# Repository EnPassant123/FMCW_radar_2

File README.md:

**FMCW Radar Project**

Contains design files, Verilog code for FPGA, and C code for computer.

Can be easily modified to act as a data streaming board (just disable sweep)

Code is still very buggy and does not pass timing. Use at your own risk!

Untested PCB changes: Added LDO to cut down on power supply noise (from USB) more.

The C code is based on libftdi1, and some changes need to be made to ftdi_stream.c

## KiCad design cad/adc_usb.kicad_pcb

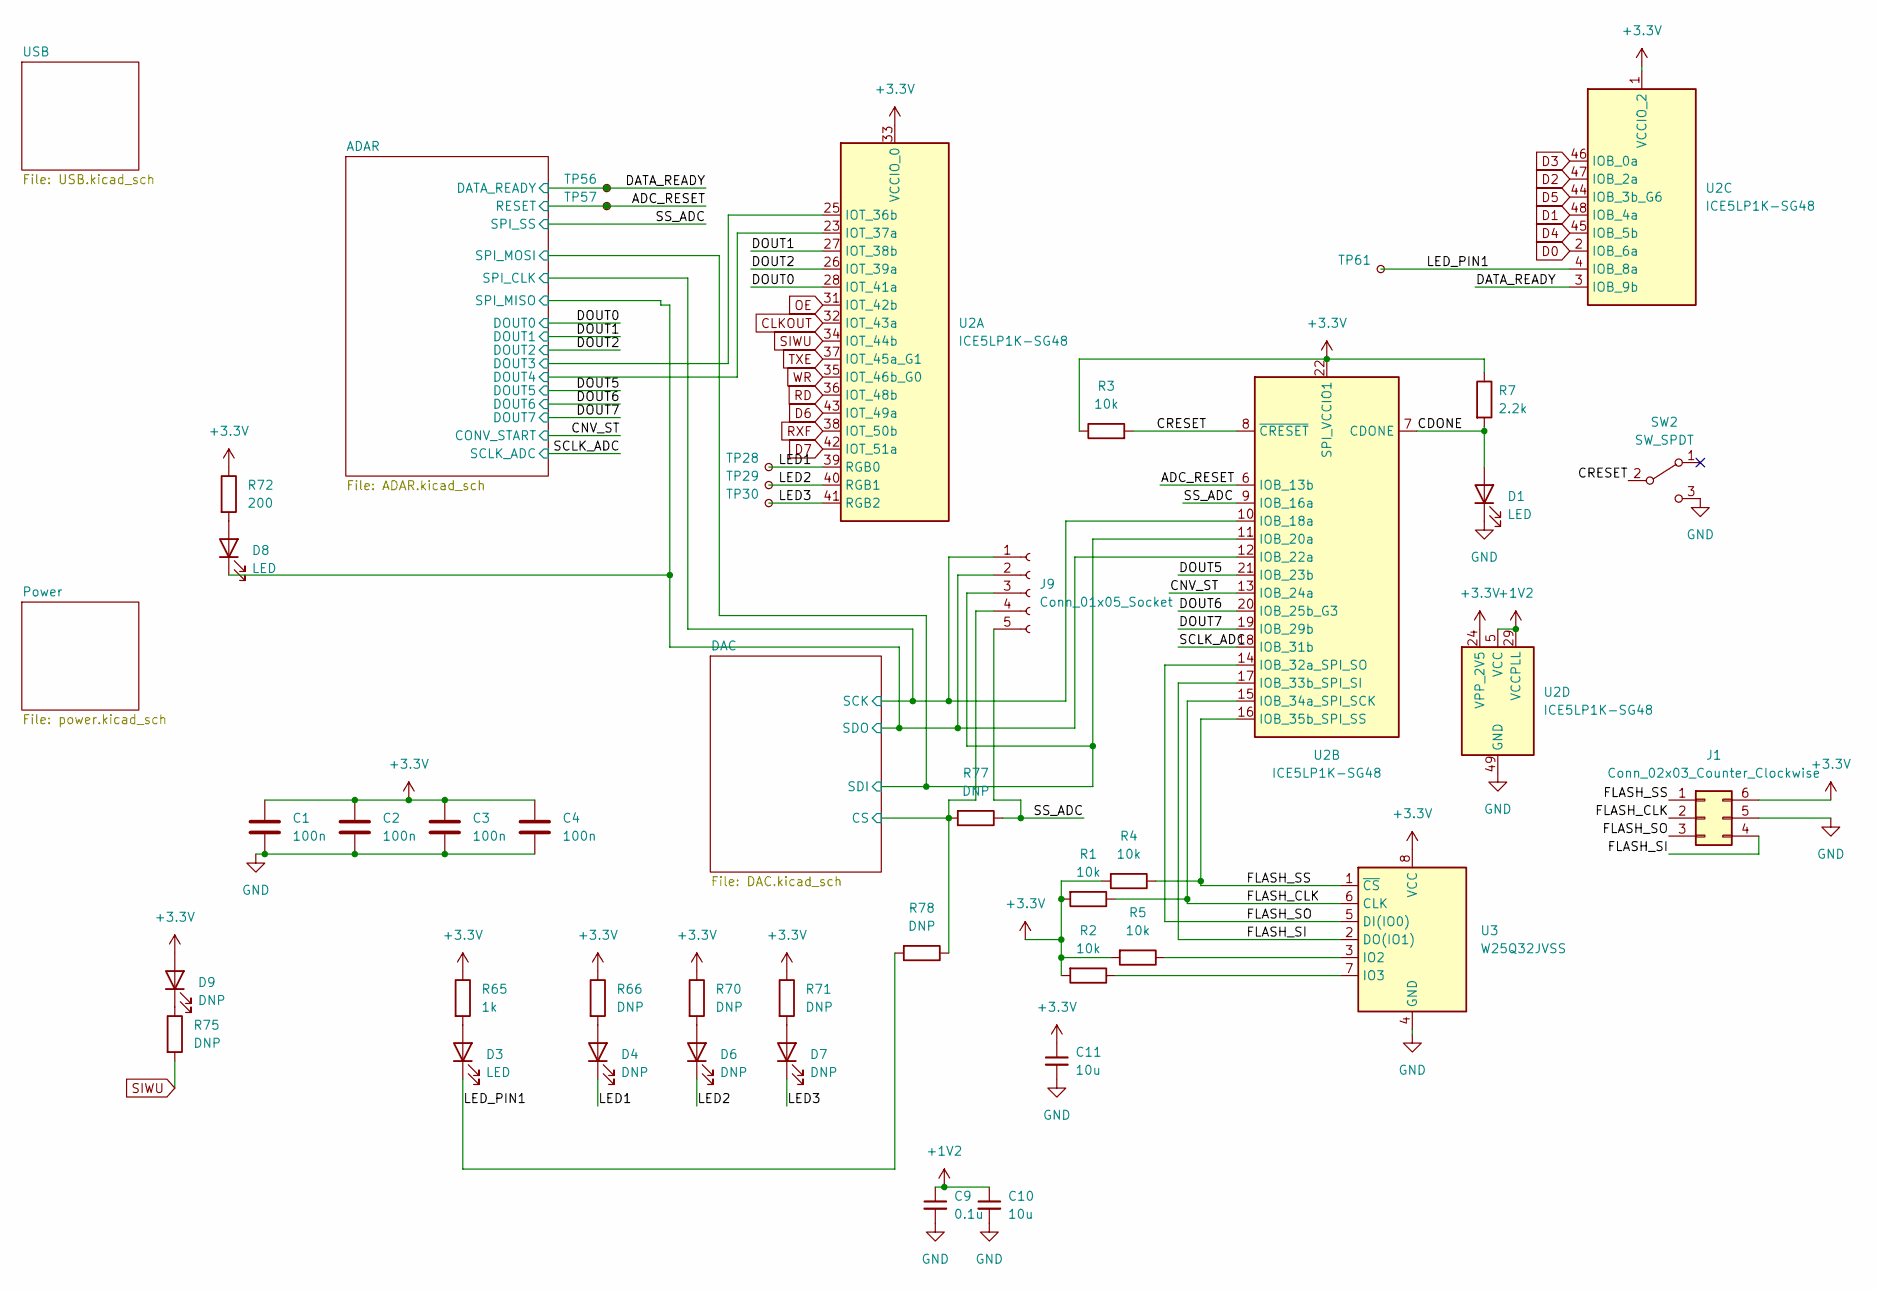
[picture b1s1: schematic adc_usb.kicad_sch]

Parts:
C1, C2, C3, C4: 100n; C_0603_1608Metric
C9: 0.1u; C_0603_1608Metric
C10, C11: 10u; C_0603_1608Metric
D1, D3, D8: LED; LED_1206_3216Metric
D4, D6, D7, D9: DNP; LED_1206_3216Metric
J1: Conn_02x03_Counter_Clockwise; PinSocket_2x03_P2.54mm_Vertical
J9: Conn_01x05_Socket; PinSocket_1x05_P2.54mm_Vertical
R1, R2, R3, R4, R5: 10k; R_0603_1608Metric
R7: 2.2k; R_0603_1608Metric
R65: 1k; R_0603_1608Metric
R66, R70, R71, R75, R77, R78: DNP; R_0603_1608Metric
R72: 200; R_0603_1608Metric
SW2: SW_SPDT; PinHeader_1x03_P2.54mm_Vertical
TP28, TP29, TP30, TP56, TP57, TP61: TestPoint_Small; TestPoint_Pad_1.0x1.0mm
U2: ICE5LP1K-SG48; QFN-48-1EP_7x7mm_P0.5mm_EP5.6x5.6mm
U3: W25Q32JVSS; SOIC-8_5.23x5.23mm_P1.27mm

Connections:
+1V2: C9.1, C10.1, U2.5 (VCC), U2.29 (VCCPLL), U2.30 (VCC); also elsewhere on the board
+3.3V: C1.1, C2.1, C3.1, C4.1, C11.1, D9.2 (A), J1.6, R1.2, R2.2, R3.1, R4.2, R5.2, R7.1, R65.1, R66.1, R70.1, R71.1, R72.1, U2.1 (VCCIO_2), U2.22 (SPI_VCCIO1), U2.24 (VPP_2V5), U2.33 (VCCIO_0), U3.8 (VCC); also elsewhere on the board
/ADAR/DOUT3: U2.25 (IOT_36b); also elsewhere on the board
/ADAR/DOUT4: U2.23 (IOT_37a); also elsewhere on the board
/ADAR/SPI_CLK: J9.1, U2.10 (IOB_18a); also elsewhere on the board
/ADAR/SPI_MISO: D8.1 (K), J9.2, U2.12 (IOB_22a); also elsewhere on the board
/ADAR/SPI_MOSI: J9.3, U2.11 (IOB_20a); also elsewhere on the board
/ADC_RESET: TP57.1, U2.6 (IOB_13b); also elsewhere on the board
/CDONE: D1.2 (A), R7.2, U2.7 (CDONE)
/CNV_ST: U2.13 (IOB_24a); also elsewhere on the board
/CRESET: R3.2, SW2.2 (B), U2.8 (~CRESET)
/DAC/CS: J9.4, R77.2, R78.1; also elsewhere on the board
/DATA_READY: TP56.1, U2.3 (IOB_9b); also elsewhere on the board
/DOUT0: U2.28 (IOT_41a); also elsewhere on the board
/DOUT1: U2.27 (IOT_38b); also elsewhere on the board
/DOUT2: U2.26 (IOT_39a); also elsewhere on the board
/DOUT5: U2.21 (IOB_23b); also elsewhere on the board
/DOUT6: U2.20 (IOB_25b_G3); also elsewhere on the board
/DOUT7: U2.19 (IOB_29b); also elsewhere on the board
/FLASH_CLK: J1.2, R1.1, U2.15 (IOB_34a_SPI_SCK), U3.6 (CLK)
/FLASH_SI: J1.4, U2.17 (IOB_33b_SPI_SI), U3.2 (DO(IO1))
/FLASH_SO: J1.3, U2.14 (IOB_32a_SPI_SO), U3.5 (DI(IO0))
/FLASH_SS: J1.1, R4.1, U2.16 (IOB_35b_SPI_SS), U3.1 (~CS)
/LED1: D4.1 (K), TP28.1, U2.39 (RGB0)
/LED2: D6.1 (K), TP29.1, U2.40 (RGB1)
/LED3: D7.1 (K), TP30.1, U2.41 (RGB2)
/LED_PIN1: D3.1 (K), R78.2, TP61.1, U2.4 (IOB_8a)
/SCLK_ADC: U2.18 (IOB_31b); also elsewhere on the board
/SS_ADC: J9.5, R77.1, U2.9 (IOB_16a); also elsewhere on the board
CLKOUT: U2.32 (IOT_43a); also elsewhere on the board
D0: U2.2 (IOB_6a); also elsewhere on the board
D1: U2.48 (IOB_4a); also elsewhere on the board
D2: U2.47 (IOB_2a); also elsewhere on the board
D3: U2.46 (IOB_0a); also elsewhere on the board
D4: U2.45 (IOB_5b); also elsewhere on the board
D5: U2.44 (IOB_3b_G6); also elsewhere on the board
D6: U2.43 (IOT_49a); also elsewhere on the board
D7: U2.42 (IOT_51a); also elsewhere on the board
GND: C1.2, C2.2, C3.2, C4.2, C9.2, C10.2, C11.2, D1.1 (K), J1.5, SW2.3 (C), U2.49 (GND), U3.4 (GND); also elsewhere on the board
unnamed: D3.2 (A), R65.2
unnamed: D4.2 (A), R66.2
unnamed: D6.2 (A), R70.2
unnamed: D7.2 (A), R71.2
unnamed: D8.2 (A), R72.2
unnamed: D9.1 (K), R75.1
unnamed: R5.1, U3.3 (IO2)
unnamed: R2.1, U3.7 (IO3)
OE: U2.31 (IOT_42b); also elsewhere on the board
RD: U2.36 (IOT_48b); also elsewhere on the board
RXF: U2.38 (IOT_50b); also elsewhere on the board
SIWU: R75.2, U2.34 (IOT_44b); also elsewhere on the board
TXE: U2.37 (IOT_45a_G1); also elsewhere on the board
WR: U2.35 (IOT_46b_G0); also elsewhere on the board

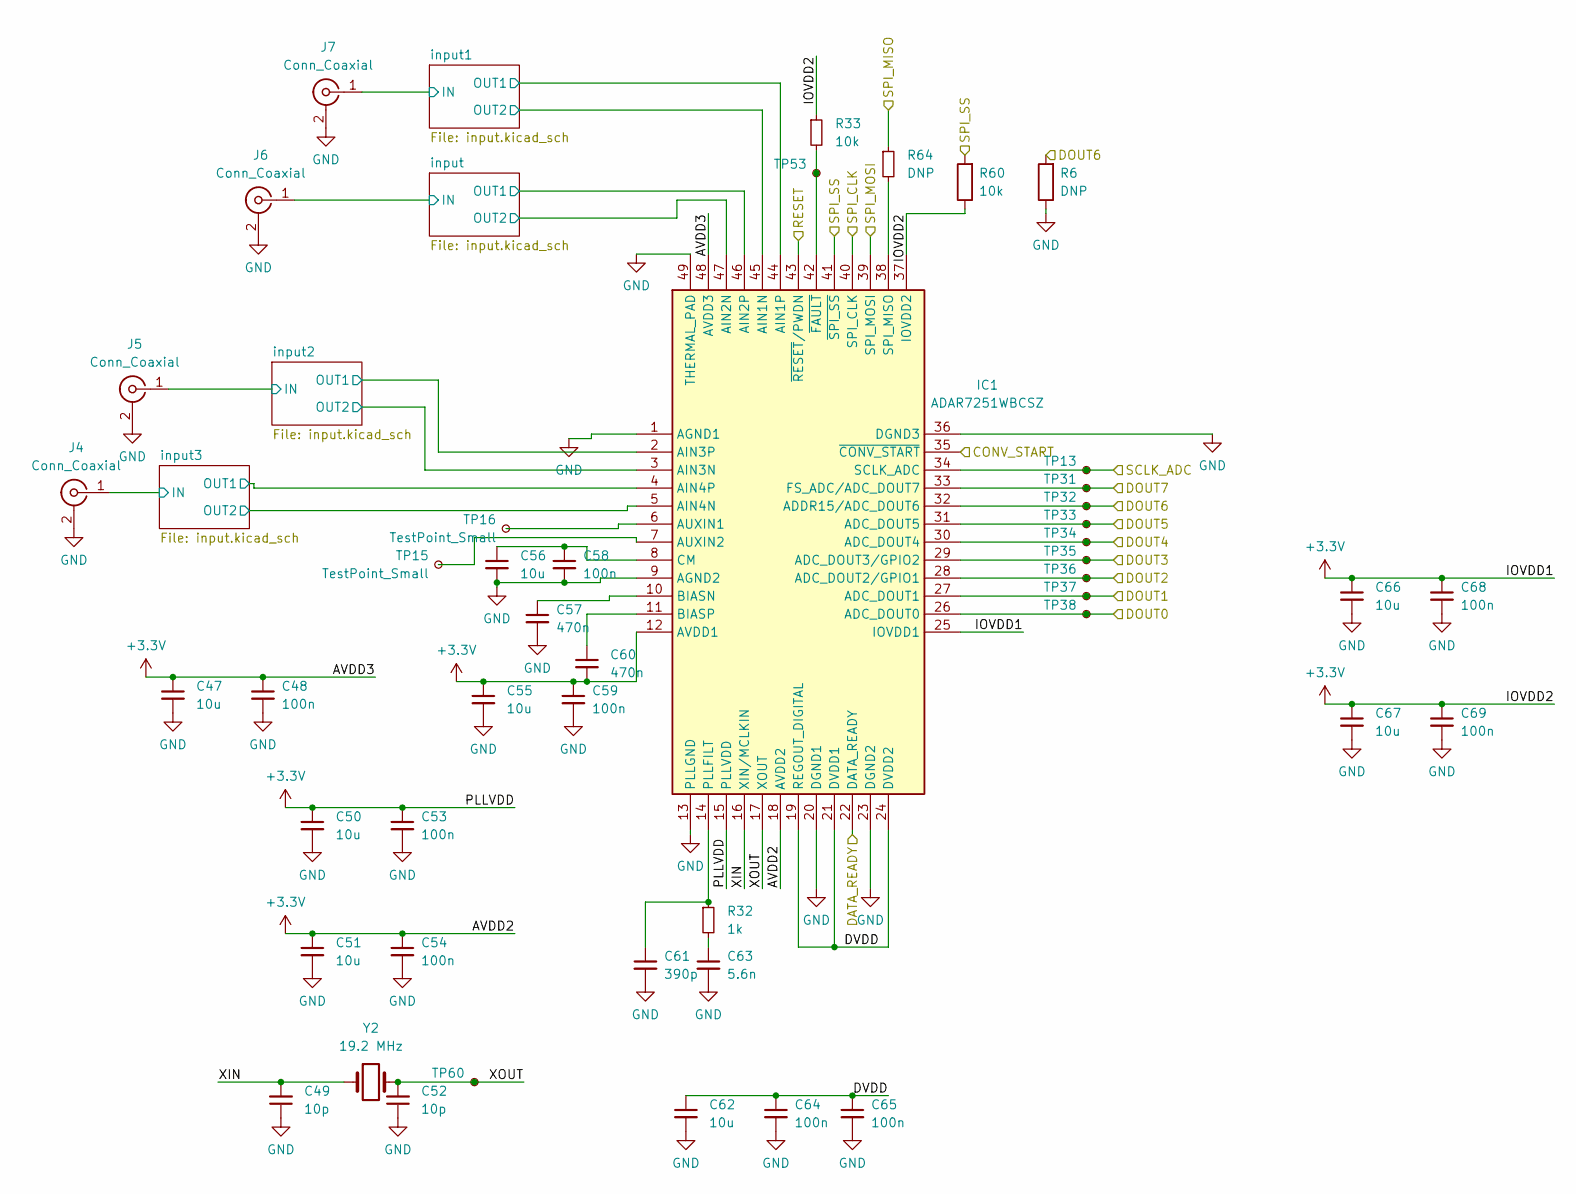
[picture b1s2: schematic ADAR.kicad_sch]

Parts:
C47, C50, C51, C55, C56, C62, C66, C67: 10u; C_0603_1608Metric
C48, C53, C54, C58, C59, C64, C65, C68, C69: 100n; C_0603_1608Metric
C49, C52: 10p; C_0603_1608Metric
C57, C60: 470n; C_0603_1608Metric
C61: 390p; C_0603_1608Metric
C63: 5.6n; C_0603_1608Metric
IC1: ADAR7251WBCSZ; LFCSP-48-1EP_7x7mm_P0.5mm_EP4.1x4.1mm; Manufacturer_Part_Number ADAR7251WBCSZ; Mouser Part Number 584-ADAR7251WBCSZ
J4, J5, J6, J7: Conn_Coaxial; SMA_Samtec_SMA-J-P-X-ST-EM1_EdgeMount
R6, R64: DNP; R_0603_1608Metric
R32: 1k; R_0603_1608Metric
R33, R60: 10k; R_0603_1608Metric
TP13, TP31, TP32, TP33, TP34, TP35, TP36, TP37, TP38, TP53: TestPoint_Small; TestPoint_Pad_1.0x1.0mm
TP15, TP16, TP60: TestPoint_Small; TestPoint_Pad_2.0x2.0mm
Y2: 19.2 MHz; Crystal_SMD_3225-4Pin_3.2x2.5mm

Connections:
+3.3V: C47.1, C48.1, C50.1, C51.1, C53.1, C54.1, C55.1, C59.1, C60.2, C66.1, C67.1, C68.1, C69.1, IC1.12 (AVDD1), IC1.15 (PLLVDD), IC1.18 (AVDD2), IC1.25 (IOVDD1), IC1.37 (IOVDD2), IC1.48 (AVDD3), R33.1, R60.1; also elsewhere on the board
/ADAR/DOUT3: IC1.29 (ADC_DOUT3/GPIO2), TP35.1; also elsewhere on the board
/ADAR/DOUT4: IC1.30 (ADC_DOUT4), TP34.1; also elsewhere on the board
/ADAR/DVDD: C62.1, C64.1, C65.1, IC1.19 (REGOUT_DIGITAL), IC1.21 (DVDD1), IC1.24 (DVDD2)
/ADAR/SPI_CLK: IC1.40 (SPI_CLK); also elsewhere on the board
/ADAR/SPI_MISO: R64.1; also elsewhere on the board
/ADAR/SPI_MOSI: IC1.39 (SPI_MOSI); also elsewhere on the board
/ADAR/XIN: C49.2, IC1.16 (XIN/MCLKIN), Y2.1
/ADAR/XOUT: C52.2, IC1.17 (XOUT), TP60.1, Y2.2
/ADAR/input1/OUT1: IC1.44 (AIN1P); also elsewhere on the board
/ADAR/input1/OUT2: IC1.45 (AIN1N); also elsewhere on the board
/ADAR/input2/IN: J5.1 (In); also elsewhere on the board
/ADAR/input2/OUT1: IC1.2 (AIN3P); also elsewhere on the board
/ADAR/input2/OUT2: IC1.3 (AIN3N); also elsewhere on the board
/ADAR/input3/OUT1: IC1.4 (AIN4P); also elsewhere on the board
/ADAR/input3/OUT2: IC1.5 (AIN4N); also elsewhere on the board
/ADAR/input/OUT1: IC1.46 (AIN2P); also elsewhere on the board
/ADAR/input/OUT2: IC1.47 (AIN2N); also elsewhere on the board
/ADC_RESET: IC1.43 (~RESET/PWDN); also elsewhere on the board
/CNV_ST: IC1.35 (~CONV_START); also elsewhere on the board
/DATA_READY: IC1.22 (DATA_READY); also elsewhere on the board
/DOUT0: IC1.26 (ADC_DOUT0), TP38.1; also elsewhere on the board
/DOUT1: IC1.27 (ADC_DOUT1), TP37.1; also elsewhere on the board
/DOUT2: IC1.28 (ADC_DOUT2/GPIO1), TP36.1; also elsewhere on the board
/DOUT5: IC1.31 (ADC_DOUT5), TP33.1; also elsewhere on the board
/DOUT6: IC1.32 (ADDR15/ADC_DOUT6), R6.2, TP32.1; also elsewhere on the board
/DOUT7: IC1.33 (FS_ADC/ADC_DOUT7), TP31.1; also elsewhere on the board
/SCLK_ADC: IC1.34 (SCLK_ADC), TP13.1; also elsewhere on the board
/SS_ADC: IC1.41 (~SPI_SS), R60.2; also elsewhere on the board
GND: C47.2, C48.2, C49.1, C50.2, C51.2, C52.1, C53.2, C54.2, C55.2, C56.2, C57.2, C58.2, C59.2, C61.2, C62.2, C63.2, C64.2, C65.2, C66.2, C67.2, C68.2, C69.2, IC1.1 (AGND1), IC1.9 (AGND2), IC1.13 (PLLGND), IC1.20 (DGND1), IC1.23 (DGND2), IC1.36 (DGND3), IC1.49 (THERMAL_PAD), J4.2 (Ext), J5.2 (Ext), J6.2 (Ext), J7.2 (Ext), R6.1; also elsewhere on the board
unnamed: C63.1, R32.2
unnamed: IC1.6 (AUXIN1), TP16.1
unnamed: IC1.7 (AUXIN2), TP15.1
unnamed: C57.1, IC1.10 (BIASN)
unnamed: C60.1, IC1.11 (BIASP)
unnamed: C56.1, C58.1, IC1.8 (CM)
unnamed: C61.1, IC1.14 (PLLFILT), R32.1
unnamed: IC1.38 (SPI_MISO), R64.2
unnamed: IC1.42 (~FAULT), R33.2, TP53.1

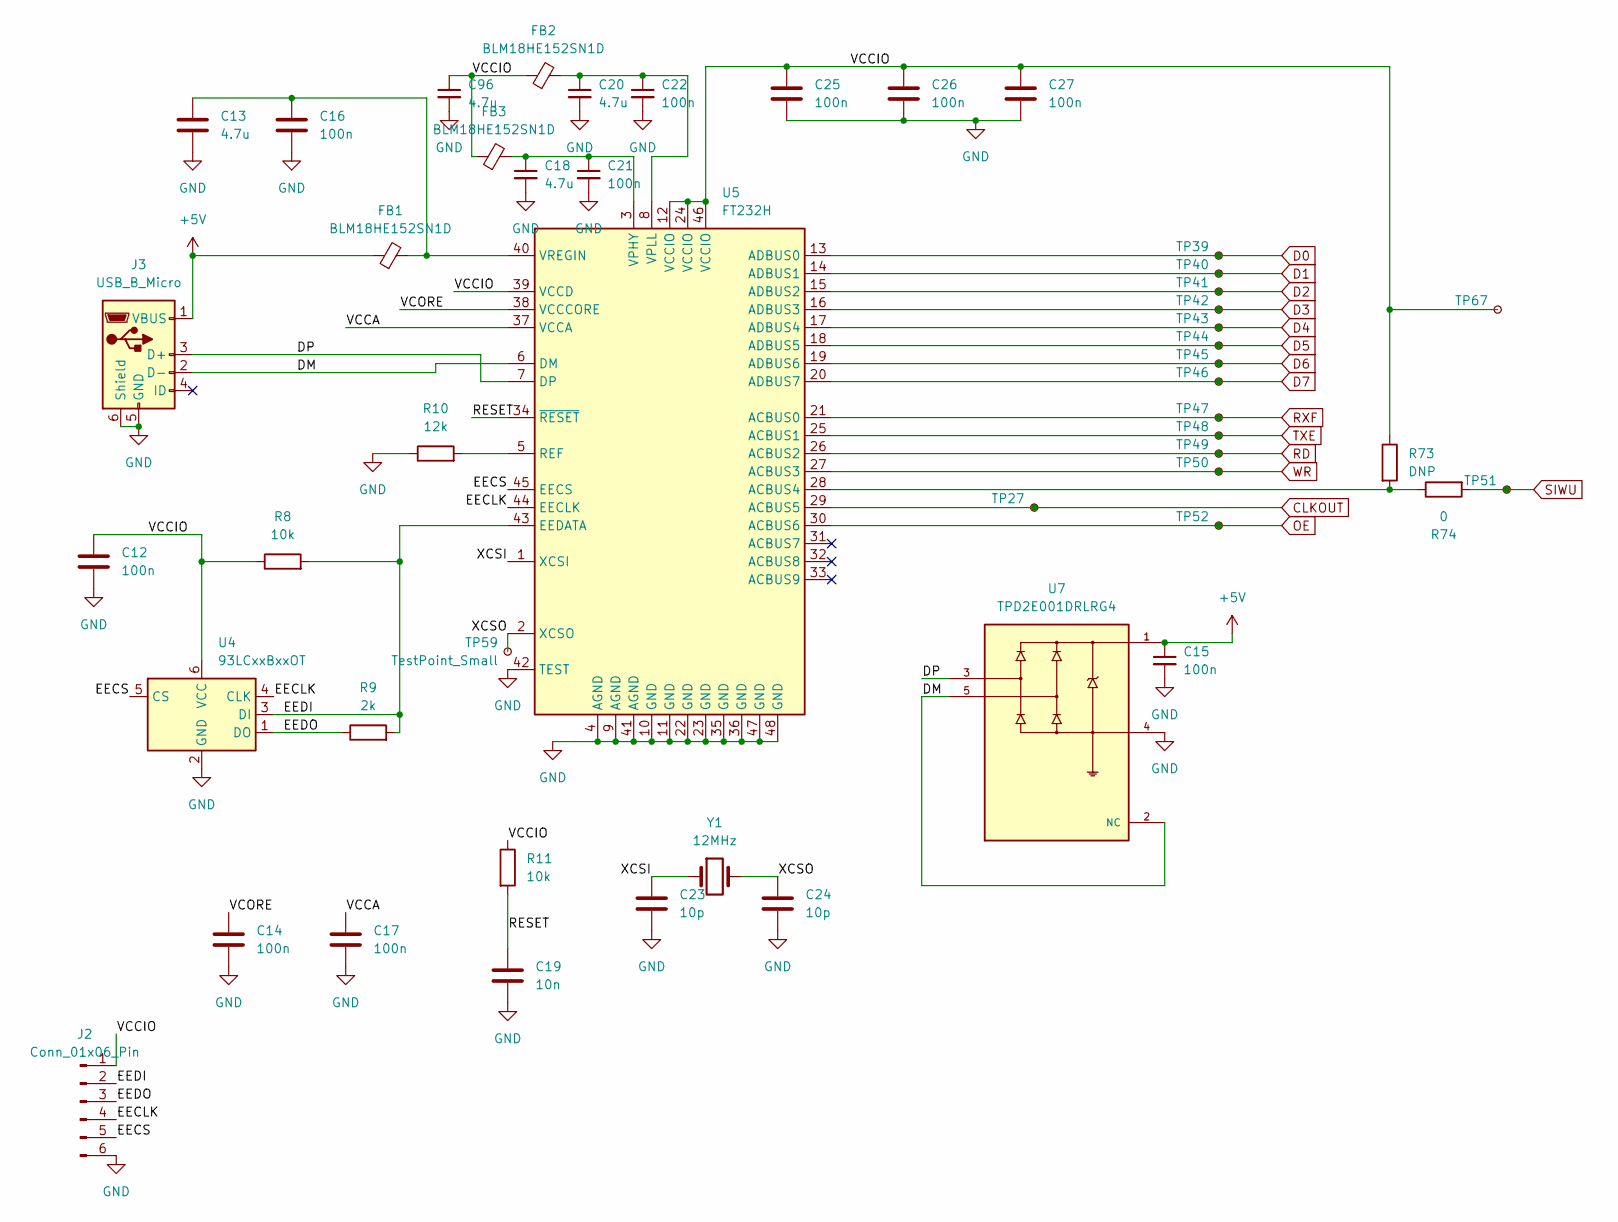
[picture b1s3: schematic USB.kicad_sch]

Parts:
C12, C14, C15, C16, C17, C21, C22, C25, C26, C27: 100n; C_0603_1608Metric
C13, C18, C20, C96: 4.7u; C_0603_1608Metric
C19: 10n; C_0603_1608Metric
C23, C24: 10p; C_0603_1608Metric
FB1, FB2, FB3: BLM18HE152SN1D; L_0603_1608Metric
J2: Conn_01x06_Pin; PinSocket_1x06_P2.54mm_Vertical
J3: USB_B_Micro; USB_Micro-B_Amphenol_10118193-0001LF_Horizontal
R8, R11: 10k; R_0603_1608Metric
R9: 2k; R_0603_1608Metric
R10: 12k; R_0603_1608Metric
R73: DNP; R_0603_1608Metric
R74: 0; R_0603_1608Metric
TP27, TP39, TP40, TP41, TP42, TP43, TP44, TP45, TP46, TP47, TP48, TP49, TP50, TP51, TP52, TP67: TestPoint_Small; TestPoint_Pad_1.0x1.0mm
TP59: TestPoint_Small; TestPoint_Pad_2.0x2.0mm
U4: 93LCxxBxxOT; SOT-23-6
U5: FT232H; LQFP-48_7x7mm_P0.5mm
U7: TPD2E001DRLRG4; SOT-553; PARTREV I
Y1: 12MHz; Crystal_SMD_3225-4Pin_3.2x2.5mm

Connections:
+5V: C15.1, FB1.1, J3.1 (VBUS), U7.1; also elsewhere on the board
/USB/DM: J3.2 (D-), U5.6 (DM), U7.2 (NC), U7.5
/USB/DP: J3.3 (D+), U5.7 (DP), U7.3
/USB/EECLK: J2.4, U4.4 (CLK), U5.44 (EECLK)
/USB/EECS: J2.5, U4.5 (CS), U5.45 (EECS)
/USB/EEDI: J2.2, R8.2, R9.2, U4.3 (DI), U5.43 (EEDATA)
/USB/EEDO: J2.3, R9.1, U4.1 (DO)
/USB/RESET: C19.1, R11.2, U5.34 (~RESET)
/USB/VCCA: C17.1, U5.37 (VCCA)
/USB/VCCIO: C12.1, C25.1, C26.1, C27.1, C96.1, FB2.1, FB3.1, J2.1, R8.1, R11.1, R73.1, TP67.1, U4.6 (VCC), U5.12 (VCCIO), U5.24 (VCCIO), U5.39 (VCCD), U5.46 (VCCIO)
/USB/VCORE: C14.1, U5.38 (VCCCORE)
/USB/XCSI: C23.1, U5.1 (XCSI), Y1.1
/USB/XCSO: C24.1, TP59.1, U5.2 (XCSO), Y1.2
CLKOUT: TP27.1, U5.29 (ACBUS5); also elsewhere on the board
D0: TP39.1, U5.13 (ADBUS0); also elsewhere on the board
D1: TP40.1, U5.14 (ADBUS1); also elsewhere on the board
D2: TP41.1, U5.15 (ADBUS2); also elsewhere on the board
D3: TP42.1, U5.16 (ADBUS3); also elsewhere on the board
D4: TP43.1, U5.17 (ADBUS4); also elsewhere on the board
D5: TP44.1, U5.18 (ADBUS5); also elsewhere on the board
D6: TP45.1, U5.19 (ADBUS6); also elsewhere on the board
D7: TP46.1, U5.20 (ADBUS7); also elsewhere on the board
GND: C12.2, C13.2, C14.2, C15.2, C16.2, C17.2, C18.2, C19.2, C20.2, C21.2, C22.2, C23.2, C24.2, C25.2, C26.2, C27.2, C96.2, J2.6, J3.5 (GND), J3.6 (Shield), R10.1, U4.2 (GND), U5.4 (AGND), U5.9 (AGND), U5.10 (GND), U5.11 (GND), U5.22 (GND), U5.23 (GND), U5.35 (GND), U5.36 (GND), U5.41 (AGND), U5.42 (TEST), U5.47 (GND), U5.48 (GND), U7.4; also elsewhere on the board
unnamed: R73.2, R74.1, U5.28 (ACBUS4)
unnamed: R10.2, U5.5 (REF)
unnamed: C18.1, C21.1, FB3.2, U5.3 (VPHY)
unnamed: C20.1, C22.1, FB2.2, U5.8 (VPLL)
unnamed: C13.1, C16.1, FB1.2, U5.40 (VREGIN)
OE: TP52.1, U5.30 (ACBUS6); also elsewhere on the board
RD: TP49.1, U5.26 (ACBUS2); also elsewhere on the board
RXF: TP47.1, U5.21 (ACBUS0); also elsewhere on the board
SIWU: R74.2, TP51.1; also elsewhere on the board
TXE: TP48.1, U5.25 (ACBUS1); also elsewhere on the board
WR: TP50.1, U5.27 (ACBUS3); also elsewhere on the board

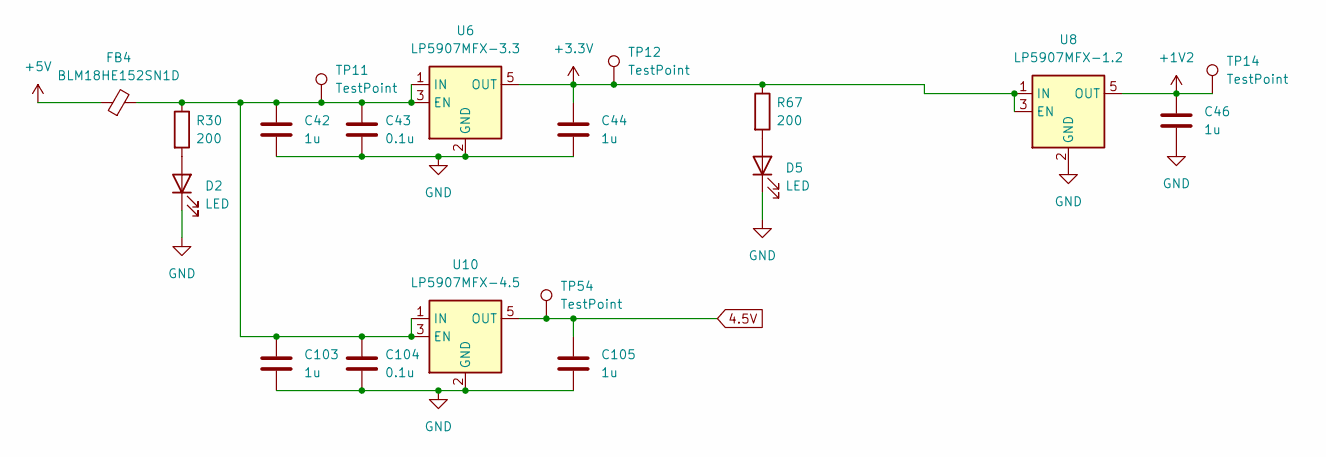
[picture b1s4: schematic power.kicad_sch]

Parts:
C42, C44, C46, C103, C105: 1u; C_0603_1608Metric
C43, C104: 0.1u; C_0603_1608Metric
D2, D5: LED; LED_1206_3216Metric
FB4: BLM18HE152SN1D; L_0603_1608Metric
R30, R67: 200; R_0603_1608Metric
TP11, TP12, TP14, TP54: TestPoint; TestPoint_Pad_2.0x2.0mm
U6: LP5907MFX-3.3; SOT-23-5
U8: LP5907MFX-1.2; SOT-23-5
U10: LP5907MFX-4.5; SOT-23-5

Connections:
4.5V: C105.1, TP54.1, U10.5 (OUT); also elsewhere on the board
+1V2: C46.1, TP14.1, U8.5 (OUT); also elsewhere on the board
+3.3V: C44.1, R67.1, TP12.1, U6.5 (OUT), U8.1 (IN), U8.3 (EN); also elsewhere on the board
+5V: FB4.1; also elsewhere on the board
GND: C42.2, C43.2, C44.2, C46.2, C103.2, C104.2, C105.2, D2.1 (K), D5.1 (K), U6.2 (GND), U8.2 (GND), U10.2 (GND); also elsewhere on the board
unnamed: D2.2 (A), R30.2
unnamed: D5.2 (A), R67.2
unnamed: C42.1, C43.1, C103.1, C104.1, FB4.2, R30.1, TP11.1, U6.1 (IN), U6.3 (EN), U10.1 (IN), U10.3 (EN)

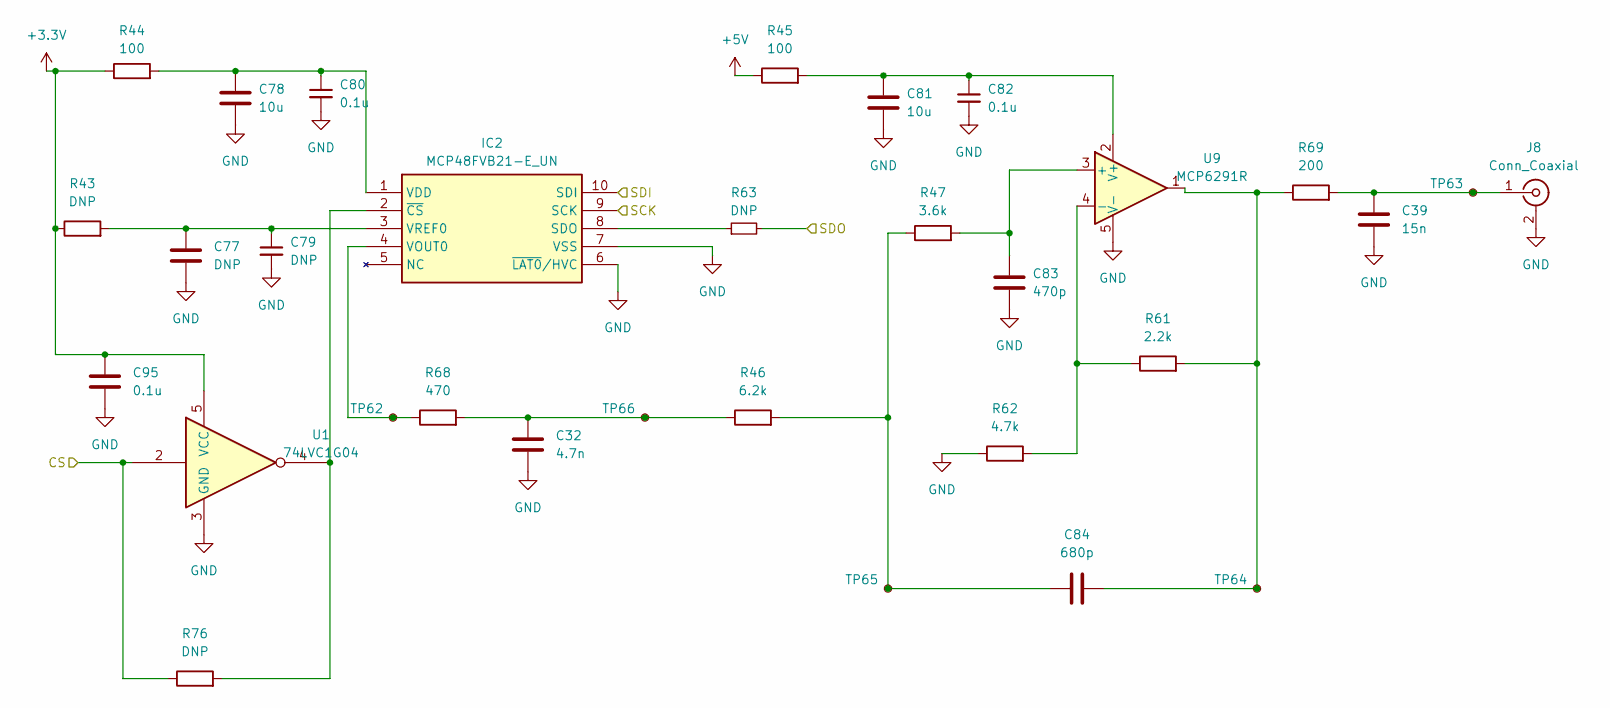
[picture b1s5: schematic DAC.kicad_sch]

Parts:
C32: 4.7n; C_0603_1608Metric
C39: 15n; C_0603_1608Metric
C77, C79: DNP; C_0603_1608Metric
C78, C81: 10u; C_0603_1608Metric
C80, C82, C95: 0.1u; C_0603_1608Metric
C83: 470p; C_0603_1608Metric
C84: 680p; C_0603_1608Metric
IC2: MCP48FVB21-E_UN; MSOP-10_3x3mm_P0.5mm; Manufacturer_Part_Number MCP48FVB21-E/UN; Mouser Part Number 579-MCP48FVB21-E/UN
J8: Conn_Coaxial; SMA_Samtec_SMA-J-P-X-ST-EM1_EdgeMount
R43, R63, R76: DNP; R_0603_1608Metric
R44, R45: 100; R_0603_1608Metric
R46: 6.2k; R_0603_1608Metric
R47: 3.6k; R_0603_1608Metric
R61: 2.2k; R_0603_1608Metric
R62: 4.7k; R_0603_1608Metric
R68: 470; R_0603_1608Metric
R69: 200; R_0603_1608Metric
TP62, TP63, TP64, TP65, TP66: TestPoint_Small; TestPoint_Pad_1.0x1.0mm
U1: 74LVC1G04; SOT-353_SC-70-5
U9: MCP6291R; SOT-23-5

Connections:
+3.3V: C95.1, R43.1, R44.1, U1.5 (VCC); also elsewhere on the board
+5V: R45.1; also elsewhere on the board
/ADAR/SPI_CLK: IC2.9 (SCK); also elsewhere on the board
/ADAR/SPI_MISO: R63.2; also elsewhere on the board
/ADAR/SPI_MOSI: IC2.10 (SDI); also elsewhere on the board
/DAC/CS: R76.1, U1.2; also elsewhere on the board
GND: C32.2, C39.2, C77.2, C78.2, C79.2, C80.2, C81.2, C82.2, C83.2, C95.2, IC2.6 (~LAT0/HVC), IC2.7 (VSS), J8.2 (Ext), R62.1, U1.3 (GND), U9.5 (V-); also elsewhere on the board
unnamed: C32.1, R46.1, R68.2, TP66.1
unnamed: C84.1, R46.2, R47.1, TP65.1
unnamed: C84.2, R61.2, R69.1, TP64.1, U9.1
unnamed: IC2.8 (SDO), R63.1
unnamed: C78.1, C80.1, IC2.1 (VDD), R44.2
unnamed: IC2.4 (VOUT0), R68.1, TP62.1
unnamed: C77.1, C79.1, IC2.3 (VREF0), R43.2
unnamed: IC2.2 (~CS), R76.2, U1.4
unnamed: C39.1, J8.1 (In), R69.2, TP63.1
unnamed: C83.1, R47.2, U9.3 (+)
unnamed: R61.1, R62.2, U9.4 (-)
unnamed: C81.1, C82.1, R45.2, U9.2 (V+)

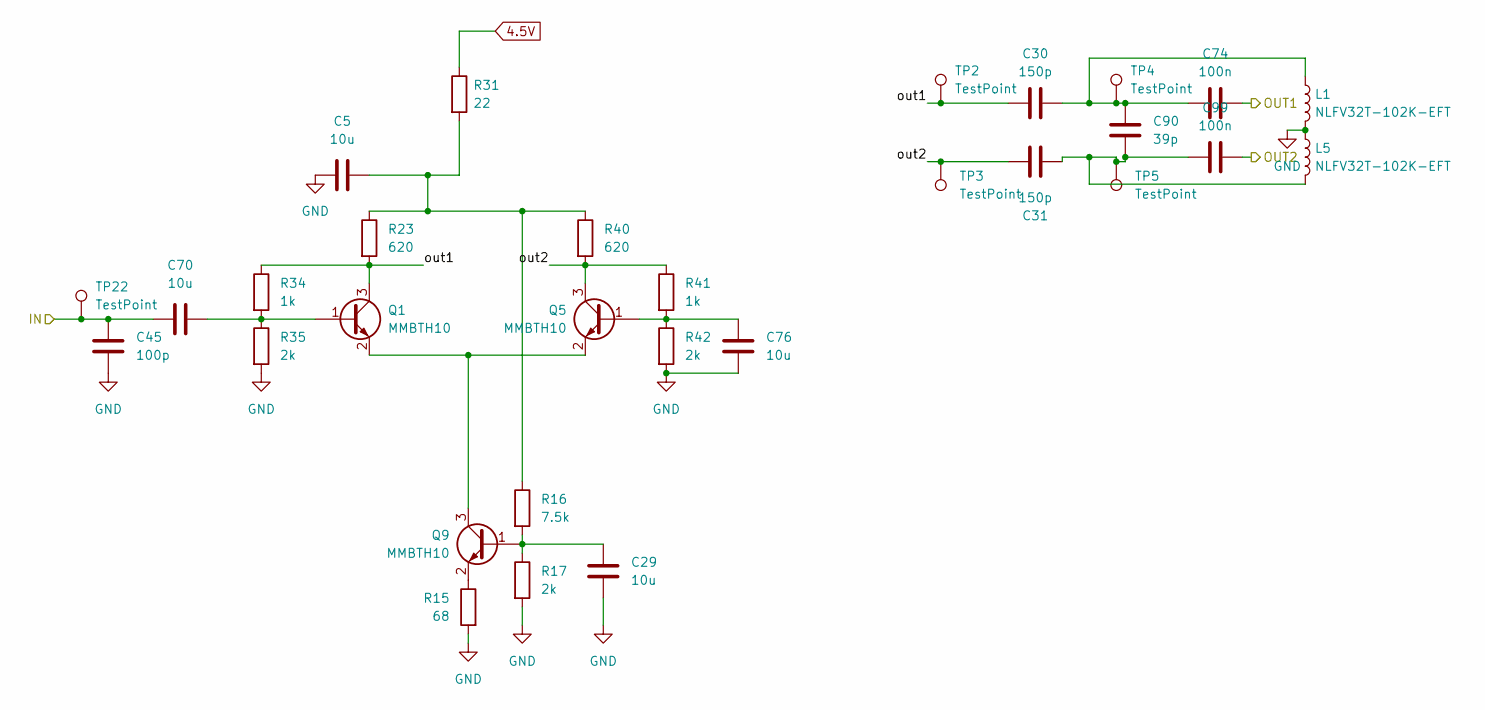
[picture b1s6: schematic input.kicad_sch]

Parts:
C5, C29, C70, C76: 10u; C_0603_1608Metric
C30, C31: 150p; C_0603_1608Metric
C45: 100p; C_0603_1608Metric
C74, C99: 100n; C_0603_1608Metric
C90: 39p; C_0603_1608Metric
L1, L5: NLFV32T-102K-EFT; L_1210_3225Metric
Q1, Q5, Q9: MMBTH10; SOT-23-3
R15: 68; R_0603_1608Metric
R16: 7.5k; R_0603_1608Metric
R17, R35, R42: 2k; R_0603_1608Metric
R23, R40: 620; R_0603_1608Metric
R31: 22; R_0603_1608Metric
R34, R41: 1k; R_0603_1608Metric
TP2, TP3, TP4, TP5, TP22: TestPoint; TestPoint_Pad_1.0x1.0mm

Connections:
4.5V: R31.1; also elsewhere on the board
/ADAR/input1/OUT1: C74.2; also elsewhere on the board
/ADAR/input1/OUT2: C99.2; also elsewhere on the board
GND: C5.1, C29.2, C45.1, C76.2, L1.2, L5.1, R15.2, R17.2, R35.2, R42.2; also elsewhere on the board
unnamed: Q1.2 (E), Q5.2 (E), Q9.3 (C)
unnamed: C29.1, Q9.1 (B), R16.2, R17.1
unnamed: Q9.2 (E), R15.1

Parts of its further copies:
C6, C7, C8, C28, C34, C35, C36, C41, C71, C85, C86, C91: 10u; C_0603_1608Metric
C33, C40, C75: 39p; C_0603_1608Metric
C37, C38, C72, C73, C87, C88: 150p; C_0603_1608Metric
C89, C97, C98, C100, C101, C102: 100n; C_0603_1608Metric
C92, C93, C94: 100p; C_0603_1608Metric
L2, L3, L4, L6, L7, L8: NLFV32T-102K-EFT; L_1210_3225Metric
Q2, Q3, Q4, Q6, Q7, Q8, Q10, Q11, Q12: MMBTH10; SOT-23-3
R12, R19, R21, R28, R48, R55: 1k; R_0603_1608Metric
R13, R20, R22, R26, R29, R39, R49, R53, R56: 2k; R_0603_1608Metric
R14, R18, R27, R36, R50, R54: 620; R_0603_1608Metric
R24, R37, R51: 68; R_0603_1608Metric
R25, R38, R52: 7.5k; R_0603_1608Metric
R57, R58, R59: 22; R_0603_1608Metric
TP1, TP6, TP7, TP8, TP9, TP10, TP17, TP18, TP19, TP20, TP21, TP23, TP24, TP25, TP26: TestPoint; TestPoint_Pad_1.0x1.0mm

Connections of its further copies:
4.5V: R57.1, R58.1, R59.1; also elsewhere on the board
/ADAR/input2/IN: C35.1, C92.2, TP6.1; also elsewhere on the board
/ADAR/input2/OUT1: C89.2; also elsewhere on the board
/ADAR/input2/OUT2: C100.2; also elsewhere on the board
/ADAR/input2/out2: C38.1, Q6.3 (C), R27.2, R28.1, TP8.1
/ADAR/input3/OUT1: C98.2; also elsewhere on the board
/ADAR/input3/OUT2: C102.2; also elsewhere on the board
/ADAR/input3/out1: C87.1, Q4.3 (C), R48.1, R50.2, TP23.1
/ADAR/input3/out2: C88.1, Q8.3 (C), R54.2, R55.1, TP24.1
/ADAR/input/OUT1: C97.2; also elsewhere on the board
/ADAR/input/OUT2: C101.2; also elsewhere on the board
GND: C6.1, C7.1, C8.1, C34.2, C36.2, C41.2, C71.2, C86.2, C91.2, C92.1, C93.1, C94.1, L2.2, L3.2, L4.2, L6.1, L7.1, L8.1, R13.2, R20.2, R22.2, R24.2, R26.2, R29.2, R37.2, R39.2, R49.2, R51.2, R53.2, R56.2; also elsewhere on the board
unnamed: C8.2, R50.1, R52.1, R54.1, R59.2
unnamed: C37.2, C40.1, C89.1, L2.1, TP9.1
unnamed: C72.2, C75.1, C97.1, L3.1, TP20.1
unnamed: C38.2, C40.2, C100.1, L6.2, TP10.1
unnamed: C73.2, C75.2, C101.1, L7.2, TP21.1
unnamed: C35.2, Q2.1 (B), R21.2, R22.1
unnamed: C85.2, Q4.1 (B), R48.2, R49.1
unnamed: C41.1, Q6.1 (B), R28.2, R29.1
unnamed: C91.1, Q8.1 (B), R55.2, R56.1
unnamed: C36.1, Q10.1 (B), R25.2, R26.1
unnamed: Q2.2 (E), Q6.2 (E), Q10.3 (C)
unnamed: Q10.2 (E), R24.1
unnamed: C71.1, Q11.1 (B), R38.2, R39.1
unnamed: Q3.2 (E), Q7.2 (E), Q11.3 (C)
unnamed: Q11.2 (E), R37.1
unnamed: C86.1, Q12.1 (B), R52.2, R53.1
unnamed: Q4.2 (E), Q8.2 (E), Q12.3 (C)
unnamed: Q12.2 (E), R51.1

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
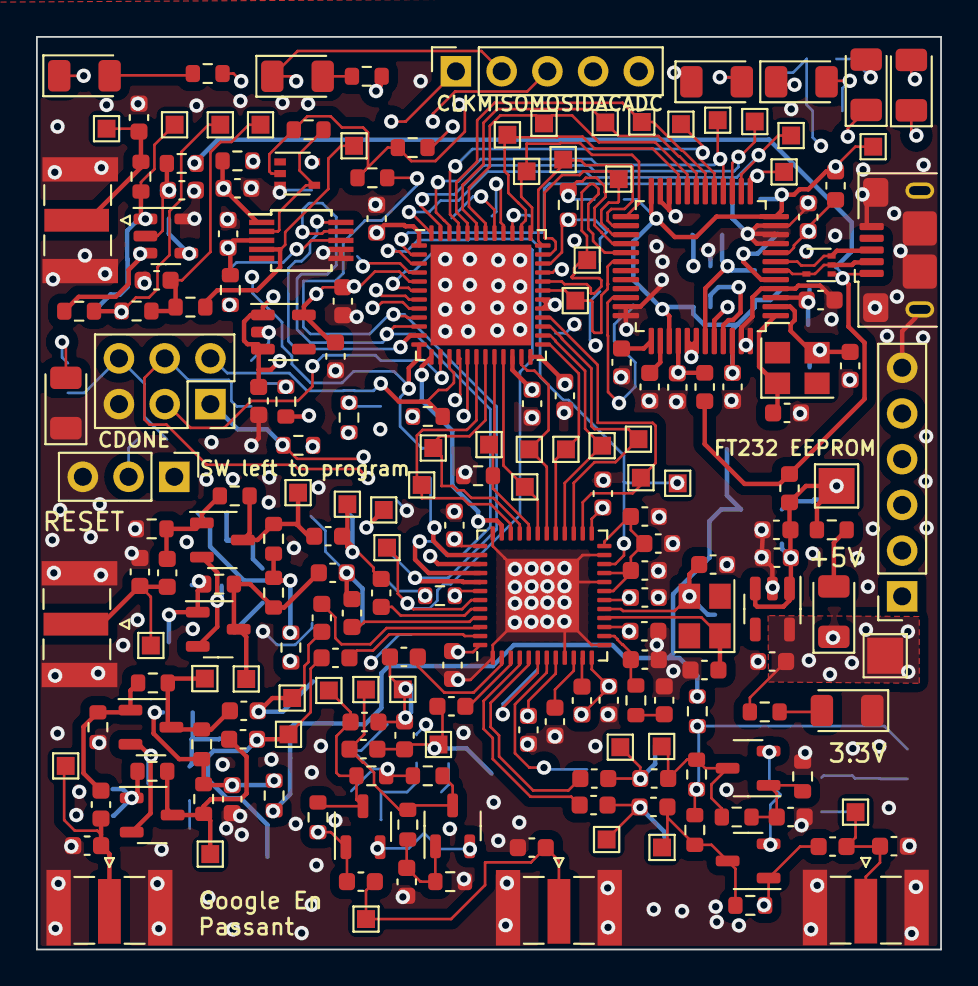
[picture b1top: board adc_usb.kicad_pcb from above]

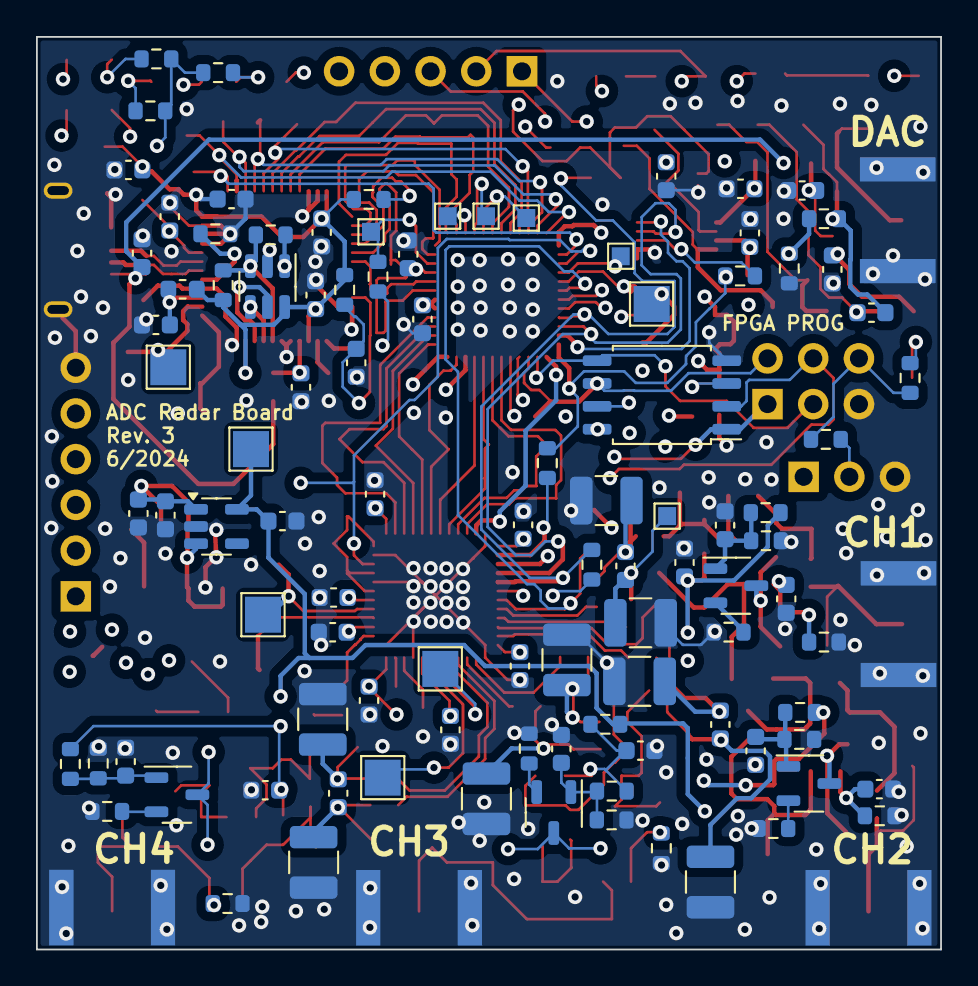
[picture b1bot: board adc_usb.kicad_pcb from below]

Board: 6 copper layers, 50.2 x 50.7 mm, 305 parts (100 on the bottom side), 151 nets.

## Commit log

2024-06-05 Create LICENSE
2024-06-05 Create test
2024-06-05 Rename ftdi_readstream_modified.c to ftdi_stream_modified.c
